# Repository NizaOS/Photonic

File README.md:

# Photonic
A Pet who blinks light 🚨🚨🚨

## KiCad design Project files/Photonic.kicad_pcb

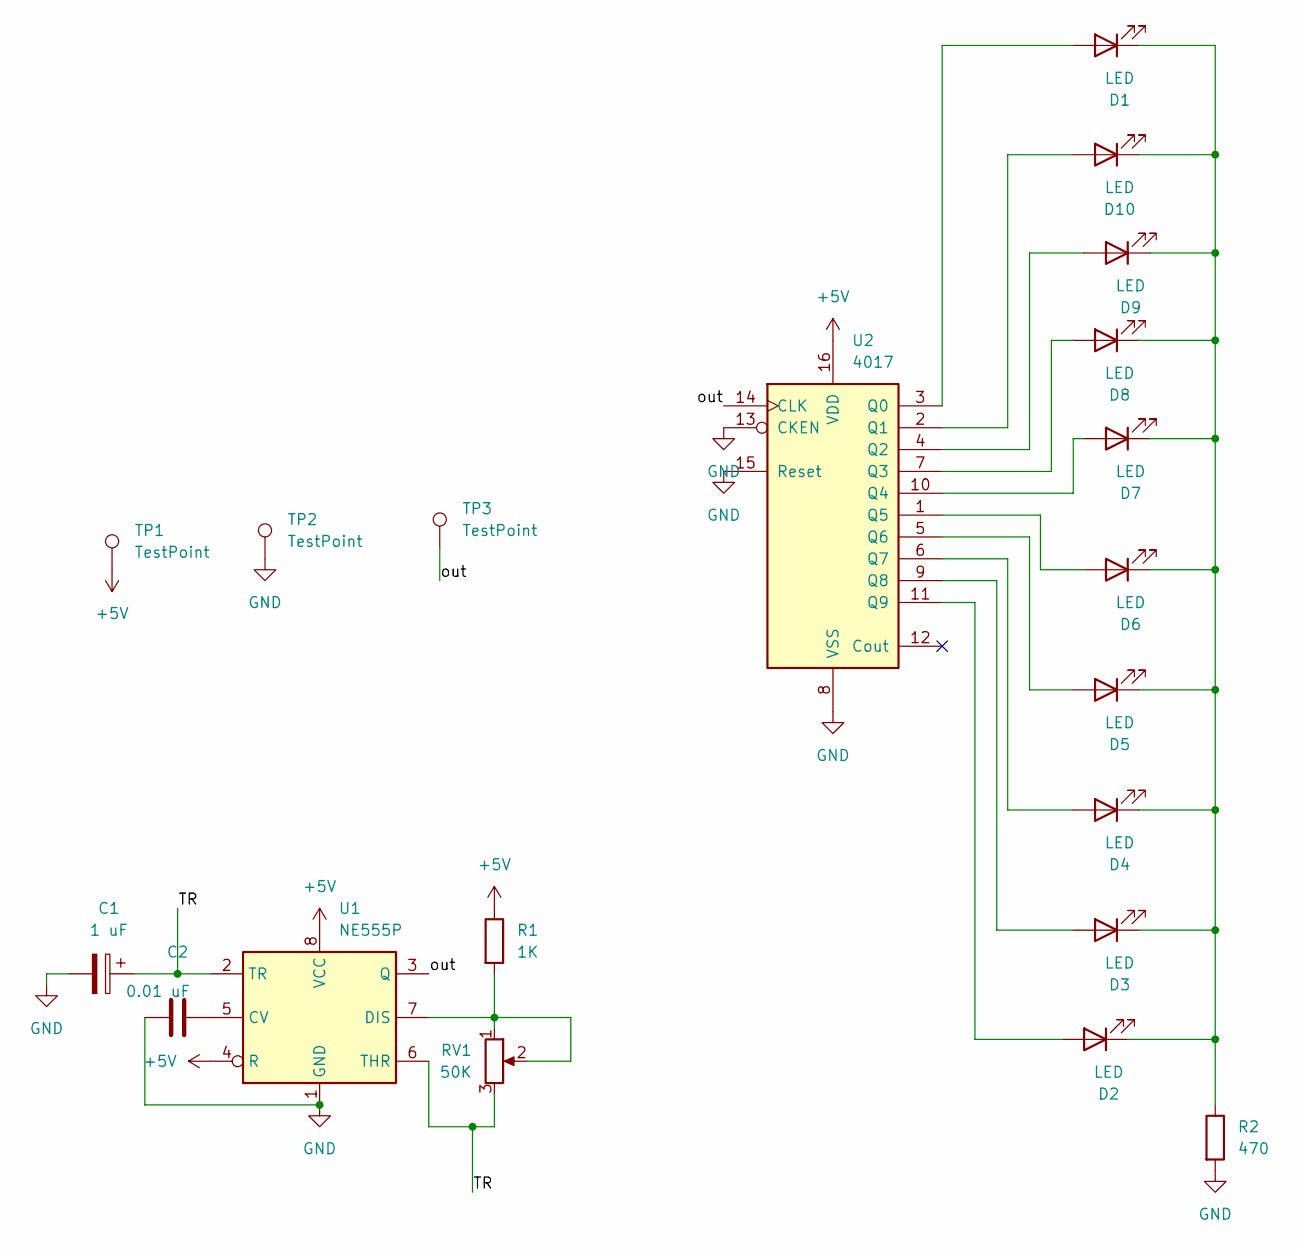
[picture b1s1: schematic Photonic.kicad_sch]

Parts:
C1: 1 uF; CP_Radial_D5.0mm_P2.00mm
C2: 0.01 uF; CP_Radial_D5.0mm_P2.00mm
D1, D2, D3, D4, D5, D6, D7, D8, D9, D10: LED; LED_D3.0mm
R1: 1K; R_Axial_DIN0207_L6.3mm_D2.5mm_P7.62mm_Horizontal
R2: 470; R_Axial_DIN0207_L6.3mm_D2.5mm_P7.62mm_Horizontal
RV1: 50K; TRIM_3362P-1-102
TP1, TP2, TP3: TestPoint; PinSocket_1x01_P2.54mm_Vertical
U1: NE555P; DIP-8_W7.62mm
U2: 4017; N16

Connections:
+5V: R1.1, TP1.1, U1.4 (R), U1.8 (VCC), U2.16 (VDD)
/TR: C1.1, RV1.3, U1.2 (TR), U1.6 (THR)
/out: TP3.1, U1.3 (Q), U2.14 (CLK)
GND: C1.2, C2.1, R2.2, TP2.1, U1.1 (GND), U2.8 (VSS), U2.13 (CKEN), U2.15 (Reset)
unnamed: D1.2 (A), U2.3 (Q0)
unnamed: D1.1 (K), D2.1 (K), D3.1 (K), D4.1 (K), D5.1 (K), D6.1 (K), D7.1 (K), D8.1 (K), D9.1 (K), D10.1 (K), R2.1
unnamed: D2.2 (A), U2.11 (Q9)
unnamed: D3.2 (A), U2.9 (Q8)
unnamed: D4.2 (A), U2.6 (Q7)
unnamed: D5.2 (A), U2.5 (Q6)
unnamed: D6.2 (A), U2.1 (Q5)
unnamed: D7.2 (A), U2.10 (Q4)
unnamed: D8.2 (A), U2.7 (Q3)
unnamed: D9.2 (A), U2.4 (Q2)
unnamed: D10.2 (A), U2.2 (Q1)
unnamed: C2.2, U1.5 (CV)
unnamed: R1.2, RV1.1, RV1.2, U1.7 (DIS)

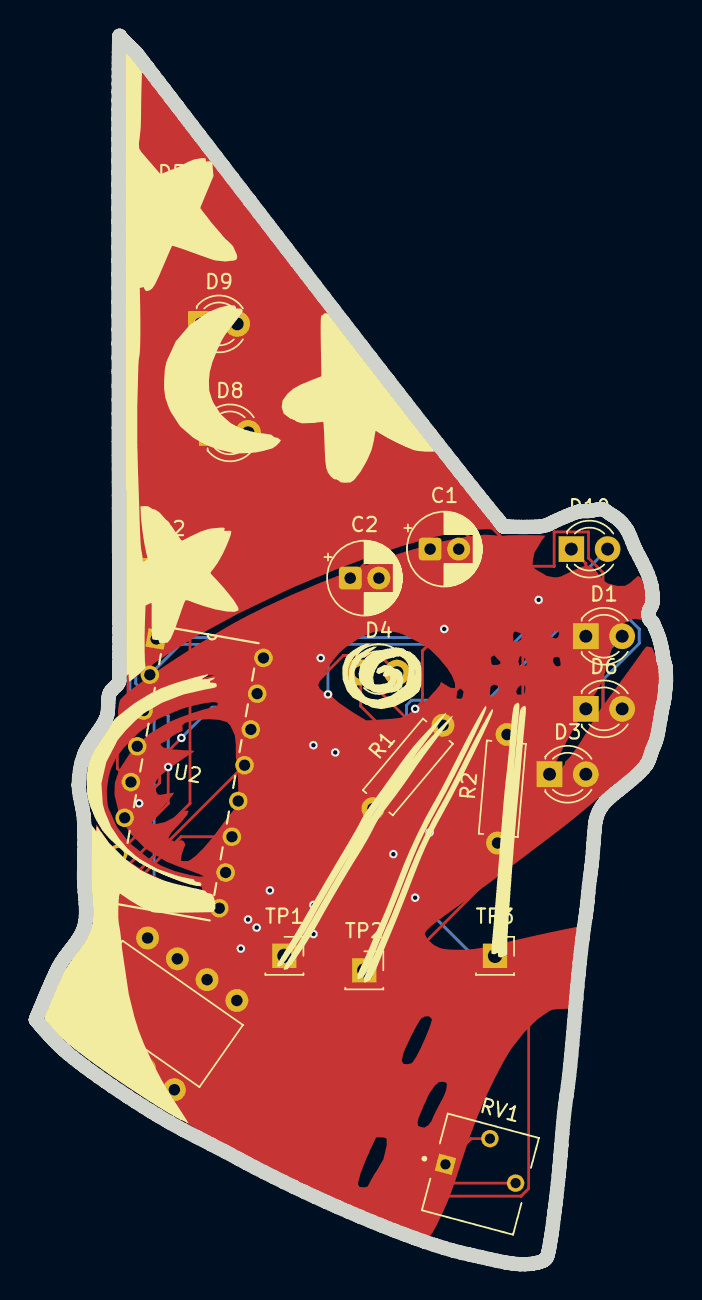
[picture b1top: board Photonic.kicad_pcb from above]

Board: 2 copper layers, 44.1 x 85.9 mm, 21 parts (0 on the bottom side), 17 nets.

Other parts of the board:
DESIGN1: DESIGN1; Graphics
